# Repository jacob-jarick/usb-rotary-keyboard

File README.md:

# usb-rotary-keyboard

**Dip Switch Settings**

| Dip | On            | Off                  |
|-----|---------------|----------------------|
| 1   | 4 Step Rotary | 2 Step Rotary        |
| 2   | Rotary Mouse  | Rotary Media Control |
| 3   | Alt Keys      | Fx Keys              |

note dip 3 change requires reset/ powercycle of keyboard.

**Cherry MX Key Functions**

| Key | Fuction | Alt Function   |
|-----|---------|----------------|
| 1   | F13     | Copy (CTRL+C)  |
| 2   | F14     | Cut (CTRL+X)   |
| 3   | F15     | Paste (CTRL+V) |
| 4   | F16     | Paste Special  |

**Keyboard mode Mappings:**

| Rotary | Left           | Right           | Click      |
|--------|----------------|-----------------|------------|
| 1      | Volume Down    | Volume Up       | Mute       |
| 2      | Media Previous | Media Next      | Pause/Play |
| 3      | Media RWD      | Media FFWD      | Media Stop |
| 4      | KEY_LEFT_ARROW | KEY_RIGHT_ARROW | SPACE      |

**Mouse mode Mappings:**

| Rotary | Left     | Right      | Click         |
|--------|----------|------------|---------------|
| 1      | Left     | Right      | Press/Release |
| 2      | Down     | Up         | Click         |
| 3      | Left Up  | Right Down | Right Click   |
| 4      | Right Up | Left Down  | Middle Click  |

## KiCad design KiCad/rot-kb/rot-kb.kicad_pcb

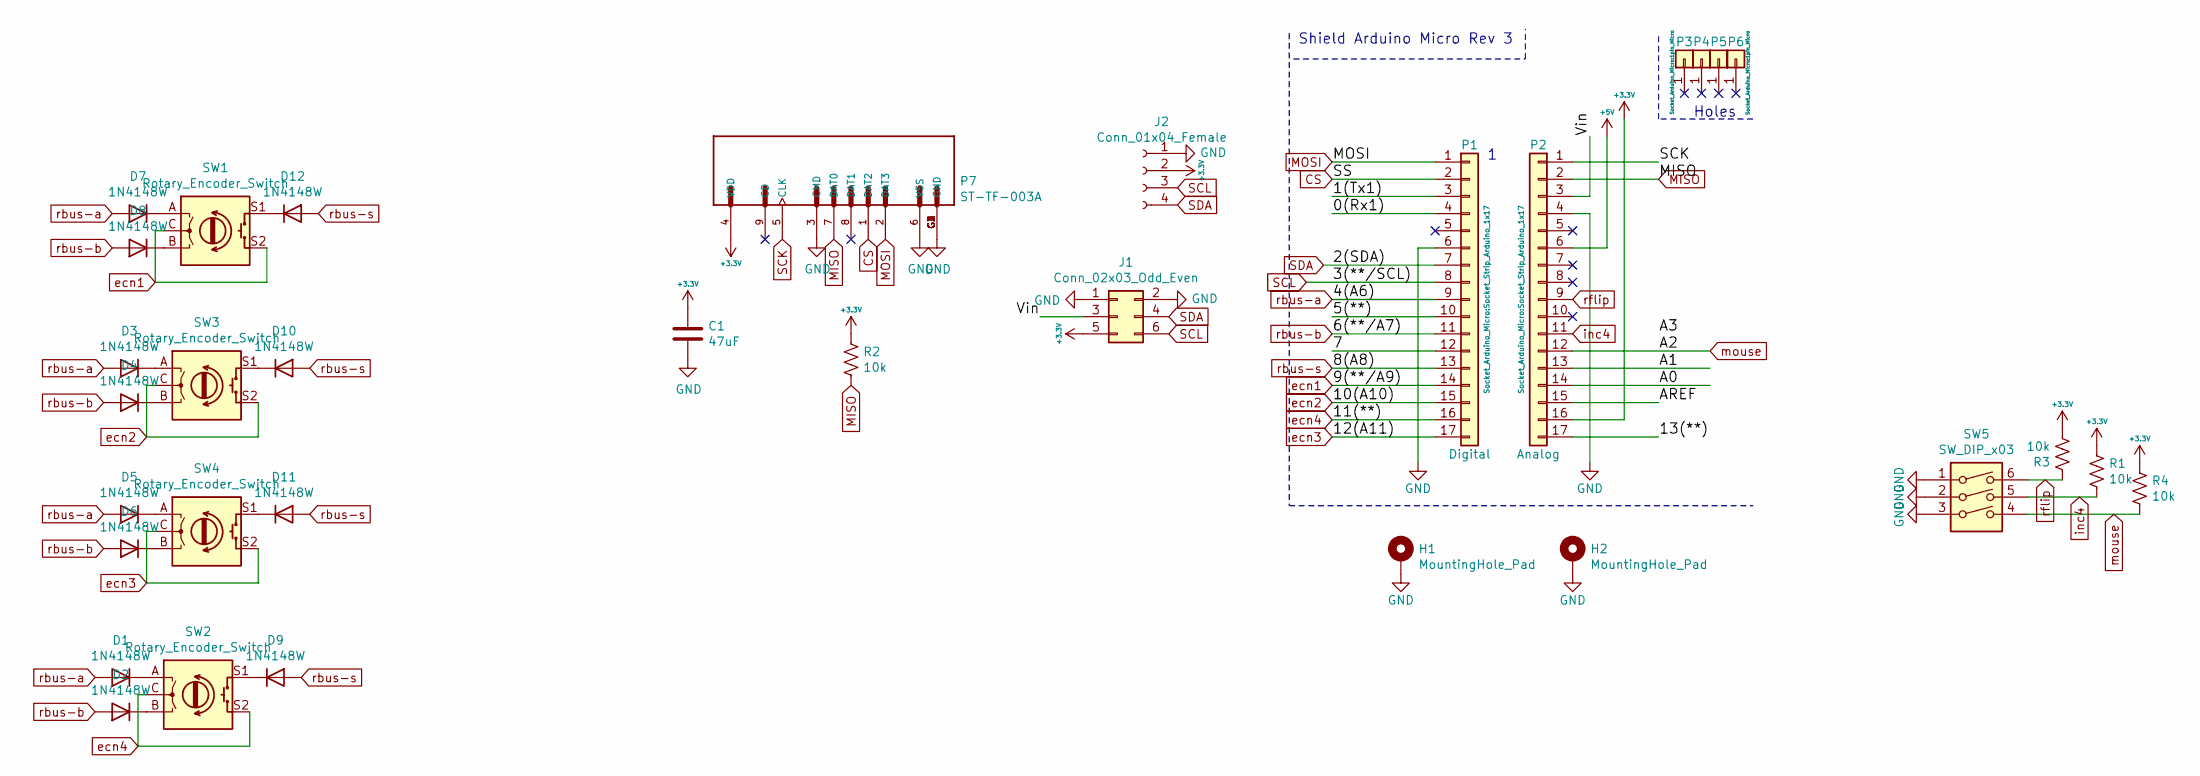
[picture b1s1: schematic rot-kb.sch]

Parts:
C1: 47uF; C_0805_2012Metric
D1, D2, D3, D4, D5, D6, D7, D8, D9, D10, D11, D12: 1N4148W; D_SOD-323_HandSoldering
H1, H2: MountingHole_Pad; MountingHole_4.3mm_M4_Pad_Via
J1: Conn_02x03_Odd_Even; IDC-Header_2x03_P2.54mm_Vertical
J2: Conn_01x04_Female; PinHeader_1x04_P2.54mm_Vertical
P1: Digital; Socket_Strip_Arduino_1x17
P2: Analog; Socket_Strip_Arduino_1x17
P3, P4, P5, P6: CONN_01X01; 1pin_Micro
P7: ST-TF-003A; SUNTECH_ST-TF-003A
R1, R2, R3, R4: 10k; R_0805_2012Metric
SW1, SW2, SW3, SW4: Rotary_Encoder_Switch; RotaryEncoder_Alps_EC11E-Switch_Vertical_H20mm
SW5: SW_DIP_x03; SW_DIP_SPSTx03_Slide_9.78x9.8mm_W7.62mm_P2.54mm

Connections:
+3V3: C1.1, J1.5, J2.2, P2.16, P7.4 (VDD), R1.1, R2.1, R3.2, R4.1
+5V: P2.6
/0(Rx1): P1.4
/1(Tx1): P1.3
/5(**): P1.10
/7: P1.12
/13(**): P2.17
/A0: P2.14
/A1: P2.13
/AREF: P2.15
/Vin: J1.3, P2.3
CS: P1.2, P7.1 (DAT2)
GND: C1.2, H1.1, H2.1, J1.1, J1.2, J2.1, P1.6, P2.4, P7.3 (CMD), P7.6 (VSS), P7.G1 (GND), P7.G2 (GND), P7.G3 (GND), P7.G4 (GND), SW5.1, SW5.2, SW5.3
MISO: P2.2, P7.7 (DAT0), R2.2
MOSI: P1.1, P7.2 (DAT3)
unnamed: D1.1 (K), SW2.A
unnamed: D2.1 (K), SW2.B
unnamed: D3.1 (K), SW3.A
unnamed: D4.1 (K), SW3.B
unnamed: D5.1 (K), SW4.A
unnamed: D6.1 (K), SW4.B
unnamed: D7.1 (K), SW1.A
unnamed: D8.1 (K), SW1.B
unnamed: D9.1 (K), SW2.S1
unnamed: D10.1 (K), SW3.S1
unnamed: D11.1 (K), SW4.S1
unnamed: D12.1 (K), SW1.S1
SCK: P2.1, P7.5 (CLK)
SCL: J1.6, J2.3, P1.8
SDA: J1.4, J2.4, P1.7
ecn1: P1.14, SW1.C, SW1.S2
ecn2: P1.15, SW3.C, SW3.S2
ecn3: P1.17, SW4.C, SW4.S2
ecn4: P1.16, SW2.C, SW2.S2
inc4: P2.11, R1.2, SW5.5
mouse: P2.12, R4.2, SW5.4
rbus-a: D1.2 (A), D3.2 (A), D5.2 (A), D7.2 (A), P1.9
rbus-b: D2.2 (A), D4.2 (A), D6.2 (A), D8.2 (A), P1.11
rbus-s: D9.2 (A), D10.2 (A), D11.2 (A), D12.2 (A), P1.13
rflip: P2.9, R3.1, SW5.6

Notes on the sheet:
Shield Arduino Micro Rev 3
Holes

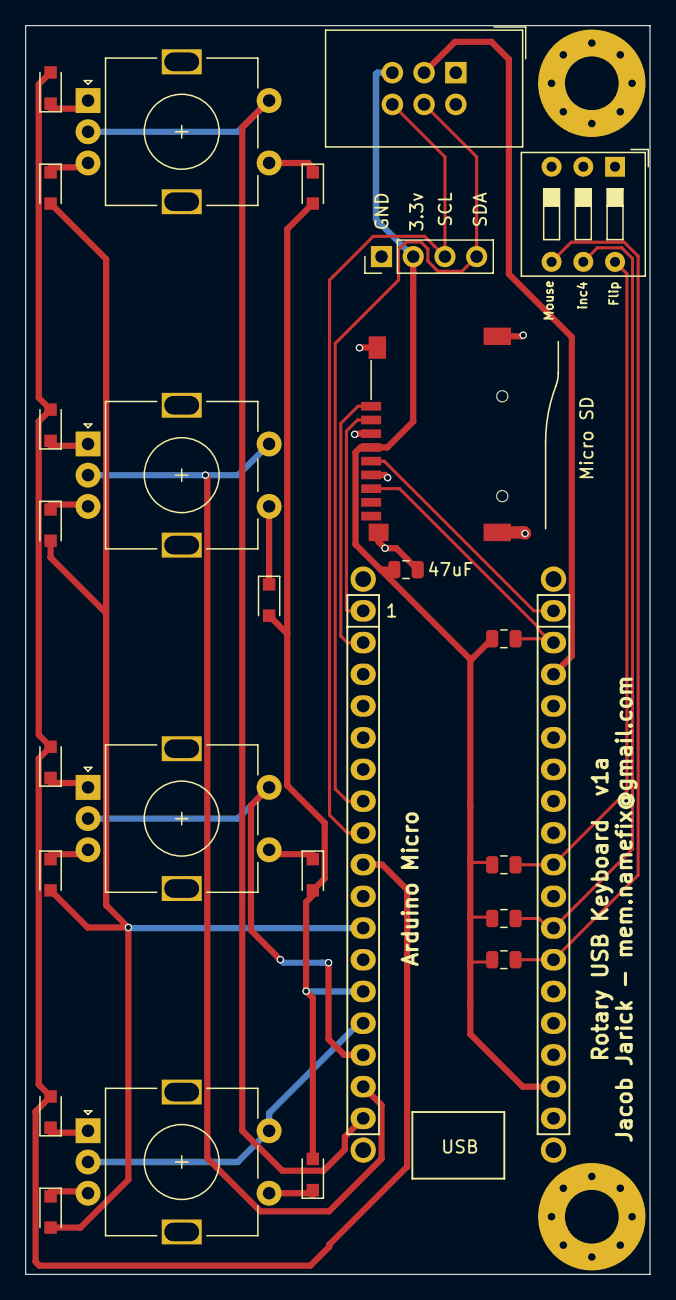
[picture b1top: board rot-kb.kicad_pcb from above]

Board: 2 copper layers, 50.0 x 100.0 mm, 33 parts (0 on the bottom side), 31 nets.

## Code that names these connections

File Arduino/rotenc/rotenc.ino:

/*  Version 1
    4x Rotary Encoder USB keyboard
    Board target: Arduino Micro Pro
    Written by Jacob Jarick
    mem.namefix@gmail.com
   https://github.com/jacob-jarick/usb-rotary-keyboard

   board: sparkfun pro micro
   5v 16Mhz
   board arduino git repo:
   https://raw.githubusercontent.com/sparkfun/Arduino_Boards/master/IDE_Board_Manager/package_sparkfun_index.json

*/

#include "HID-Project.h"
#include <CommonBusEncoders.h>
CommonBusEncoders encoders(4, 6, 8, 4);

const bool skyrim_photos = 1;

const uint8_t keya = 19;
const uint8_t keyb = 7;
const uint8_t keyc = 22;
const uint8_t keyd = 5;

const int sky_inc = 300;

const uint8_t dip1 = 23; // rflip (now paste special) - triggers keyC
const uint8_t dip2 = 21; // mouse
const uint8_t dip3 = 20; // inc4

const uint8_t key_debounce = 150;

unsigned long keysleep[8] = {0, 0, 0, 0, 0, 0, 0, 0};

// set to match your encoders.
uint8_t rsteps = 2;

// these bools will be set via jumpers
//bool alt_steps = 1; // 0 = 2 steps, 1 = 4 steps
bool rmouse = 0; // worlds most awkward mouse - etch a sketch style

// internal bools

bool mousepress = 0;

void setup()
{
  pinMode(keya, INPUT);
  pinMode(keyb, INPUT);
  pinMode(keyc, INPUT);
  pinMode(keyd, INPUT);

  pinMode(dip1, INPUT);
  pinMode(dip2, INPUT);
  pinMode(dip3, INPUT);

  encoders.setDebounce(16);
  encoders.resetChronoAfter(1000);

  if (digitalRead(dip3))
    rsteps = 4;

  encoders.addEncoder(1, rsteps, 12, 1, 100,  199);
  encoders.addEncoder(2, rsteps, 11, 1, 200, 299);
  encoders.addEncoder(3, rsteps, 10, 1, 300,  399);
  encoders.addEncoder(4, rsteps, 9, 1, 400, 499);

  Consumer.begin();
  Keyboard.begin();
  Mouse.begin();

  Serial.begin(19200);
}

void loop()
{
  // ====================================================
  // read dip switches

  rmouse = digitalRead(dip2);
  uint8_t alt_keymap = digitalRead(dip1);

  // ====================================================
  // read keys

  if (keysleep[0] < millis() && !digitalRead(keya))
  {
    keysleep[0] = millis() + key_debounce;

    if (skyrim_photos)
    {
      Mouse.move(sky_inc * 2, 0, 0);
      delay(100);
      macro_shift_fx(12);
      keysleep[0] = millis() + 750;
    }
    else if (alt_keymap)
      macro_copy();
    else
      macro_shift_fx(1);
  }
  if (keysleep[1] < millis() && !digitalRead(keyb))
  {
    keysleep[1] = millis() + key_debounce;

    if (skyrim_photos)
    {
      Mouse.move(0, sky_inc * -1, 0);
      delay(100);
      macro_shift_fx(12);
      keysleep[1] = millis() + 750;
    }
    else if (alt_keymap)
      macro_cut();
    else
      macro_shift_fx(2);
  }
  if (keysleep[2] < millis() && !digitalRead(keyc))
  {
    keysleep[2] = millis() + key_debounce;

    if (alt_keymap)
      macro_paste();
    else
      macro_shift_fx(3);
  }
  if (keysleep[3] < millis() && !digitalRead(keyd))
  {
    keysleep[3] = millis() + key_debounce;

    if (alt_keymap)
      macro_paste_special();
    else
      macro_shift_fx(4);
  }

  // ====================================================
  // read encoders

  int index = encoders.readAll();
  if (index == 0)
    return;

  Serial.println(index);

  // ----------------------------------------
  // Rotary 1 - media vol, up, down, mute

  if (keysleep[4] < millis())
  {
    if (index == 101)
    {
      keysleep[4] = millis() + key_debounce;

      if (rmouse)
      {
        if (skyrim_photos)
        {
          Mouse.move(sky_inc * 2, 0, 0);
          delay(100);
          macro_shift_fx(12);
        }
        else
        {
          Mouse.move(5, 0, 0);
        }
      }
      else
        Consumer.write(MEDIA_VOLUME_UP);
    }
    else if (index == 100)
    {
      keysleep[4] = millis() + key_debounce;

      if (rmouse)
      {
        if (skyrim_photos)
        {
          Mouse.move(sky_inc * -2, 0, 0);
          delay(100);
          macro_shift_fx(12);
        }
        else
          Mouse.move(-5, 0, 0);
      }
      else
        Consumer.write(MEDIA_VOLUME_DOWN);
    }
    else if (index == 199)
    {
      keysleep[4] = millis() + key_debounce;

      if (rmouse)
        mousetoggle();
      else
        Consumer.write(MEDIA_VOLUME_MUTE);
    }
  }

  // ----------------------------------------
  // Rotary 2 - media, next, prev, play/pause

  if (keysleep[5] < millis())
  {
    if (index == 201)
    {
      keysleep[5] = millis() + key_debounce;

      if (rmouse)
      {
        if (skyrim_photos)
        {
          Mouse.move(0, sky_inc, 0);
          delay(100);
          macro_shift_fx(12);
        }
        else
          Mouse.move(0, 5, 0);
      }
      else
        Consumer.write(MEDIA_NEXT);
    }
    else if (index == 200)
    {
      keysleep[5] = millis() + key_debounce;
      if (rmouse)
      {
        if (skyrim_photos)
        {
          Mouse.move(0, sky_inc * -1, 0);
          delay(100);
          macro_shift_fx(12);
        }
        else
          Mouse.move(0, -5, 0);
      }
      else
        Consumer.write(MEDIA_PREVIOUS);
    }
    else if (index == 299)
    {
      keysleep[5] = millis() + key_debounce;
      if (rmouse)
      {
        Mouse.release();
        Mouse.click();
      }
      else
        Consumer.write(MEDIA_PLAY_PAUSE);
    }
  }
  // ----------------------------------------
  // Rotary 3 - media ffwd, rwd, stop

  if (keysleep[6] < millis())
  {
    if (index == 301)
    {
      keysleep[6] = millis() + key_debounce;

      if (rmouse)
        Mouse.move(5, 5, 0);
      else

        Consumer.write(MEDIA_FAST_FORWARD);
    }
    else if (index == 300)
    {
      keysleep[6] = millis() + key_debounce;

      if (rmouse)
        Mouse.move(-5, -5, 0);
      else
        Consumer.write(MEDIA_REWIND);
    }
    else if (index == 399)
    {
      keysleep[6] = millis() + key_debounce;

      if (rmouse)
      {
        Mouse.release();
        Mouse.click(MOUSE_RIGHT);
      }
      else
        Consumer.write(MEDIA_STOP);
    }
  }
  // ----------------------------------------
  // Rotary 4 - mplayer control

  if (keysleep[7] < millis())
  {
    if (index == 401)
    {
      keysleep[7] = millis() + key_debounce;

      if (rmouse)
        Mouse.move(-5, 5, 0);
      else
        Keyboard.write(KEY_RIGHT_ARROW);
    }
    else if (index == 400)
    {
      keysleep[7] = millis() + key_debounce;

      if (rmouse)
        Mouse.move(5, -5, 0);
      else
        Keyboard.write(KEY_LEFT_ARROW);
    }
    else if (index == 499)
    {
      keysleep[7] = millis() + key_debounce;

      if (rmouse)
      {
        Mouse.release();
        Mouse.click(MOUSE_MIDDLE);
      }
      else
        Keyboard.write(' ');
    }
  }
}

void mousetoggle()
{
  mousepress = !mousepress;

  if (mousepress)
    Mouse.press();
  else
    Mouse.release();
}


void macro_paste()
{
  Serial.println("C - Paste");
  Keyboard.press(KEY_LEFT_CTRL);
  Keyboard.press('v');
  delay(50);
  Keyboard.releaseAll();
}

void macro_cut()
{
  Serial.println("B - Cut");
  Keyboard.press(KEY_LEFT_CTRL);
  Keyboard.press('x');
  delay(50);
  Keyboard.releaseAll();
}

void macro_copy()
{
  Serial.println("A - Copy");
  Keyboard.press(KEY_LEFT_CTRL);
  Keyboard.press('c');
  delay(50);
  Keyboard.releaseAll();
}

void macro_paste_special()
{
  Serial.println("D - Paste Special");

  // jump to begining of form input/ line
  Keyboard.write(KEY_HOME);
  delay(50);

  // select contents of form input/ line
  Keyboard.press(KEY_LEFT_SHIFT);
  Keyboard.press(KEY_END);
  delay(50);

  Keyboard.releaseAll();
  delay(50);

  // delete contents
  Keyboard.write(KEY_DELETE);
  delay(50);

  // paste clipboard contents
  Keyboard.press(KEY_LEFT_CTRL);
  Keyboard.press('v');
  delay(50);
  Keyboard.releaseAll();
}

void macro_shift_fx(uint8_t fx)
{
  Serial.println("F" + String(fx));

  Keyboard.press(KEY_LEFT_SHIFT);

  if (fx == 1)
    Keyboard.press(KEY_F1);
  else if (fx == 2)
    Keyboard.press(KEY_F2);
  else if (fx == 3)
    Keyboard.press(KEY_F3);
  else if (fx == 4)
    Keyboard.press(KEY_F4);
  else if (fx == 12)
    Keyboard.press(KEY_F12);

  delay(50);
  Keyboard.releaseAll();
}

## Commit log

2020-07-26 more media controls
2020-07-26 mplayer keybindings
2020-07-26 docs
2020-07-26 mouse mode
2020-11-12 v2 keyboard
2020-11-14 dips, Fx Keys
